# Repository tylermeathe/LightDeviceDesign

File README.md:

# LightDeviceDesign
This read me file is a description of the project.

In this project, one needs to create a light device that functions under different conditions. The light must be able to turn off, turn on at a bright level, be on at an intermediate bright level, be on at a least bright level, and also be on in 2 Hz intervals. The device should be protected by its casing and able to withstand a 3 ft fall as well.

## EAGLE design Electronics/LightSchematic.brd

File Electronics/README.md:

# LightDeviceDesign
This read me file is a description of the project.

In this project, one needs to create a light device that functions under different conditions. The light must be able to turn off, turn on at a bright level, be on at an intermediate bright level, be on at a least bright level, and also be on in 2 Hz intervals. The device should be protected by its casing and able to withstand a 3 ft fall as well.

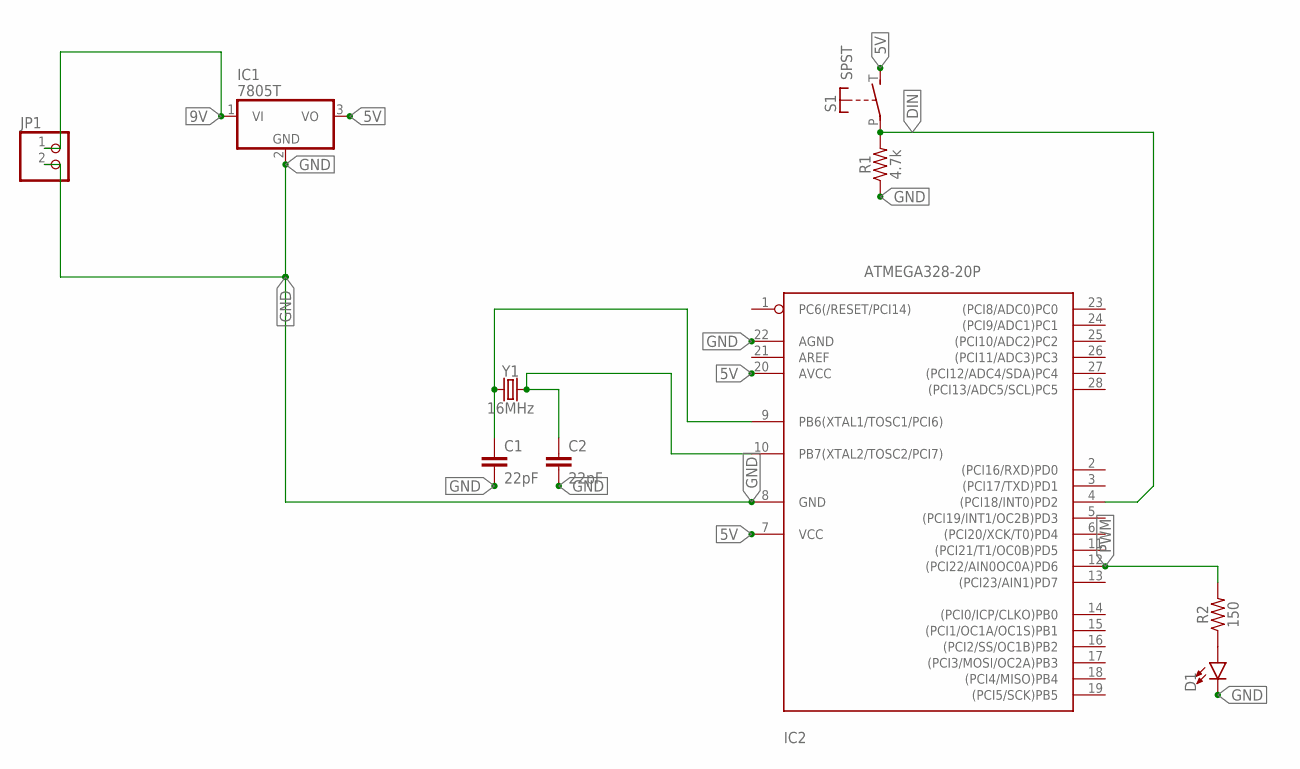
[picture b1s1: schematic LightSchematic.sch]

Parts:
C1, C2: 22pF; 0603
D1: LED1206; LED-1206
IC1: 7805T; TO220H
IC2: ATMEGA328-20P; DIL28-3
JP1: PINHD-1X2; 1X02
R1: 4.7k; 0402
R2: 150; 0402
S1: SPST; JUDCOSPST
Y1: 16MHz; HC49US

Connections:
5V: IC1.3 (VO), IC2.7 (VCC), IC2.20 (AVCC), S1.T (S)
9V: IC1.1 (VI), JP1.1
DIN: IC2.4 ((PCI18/INT0)PD2), R1.2, S1.P
GND: C1.2, C2.2, D1.C, IC1.2 (GND), IC2.8 (GND), IC2.22 (AGND), JP1.2, R1.1
unnamed: C1.1, IC2.9 (PB6(XTAL1/TOSC1/PCI6)), Y1.1
unnamed: C2.1, IC2.10 (PB7(XTAL2/TOSC2/PCI7)), Y1.2
unnamed: D1.A, R2.1
PWM: IC2.12 ((PCI22/AIN0OC0A)PD6), R2.2

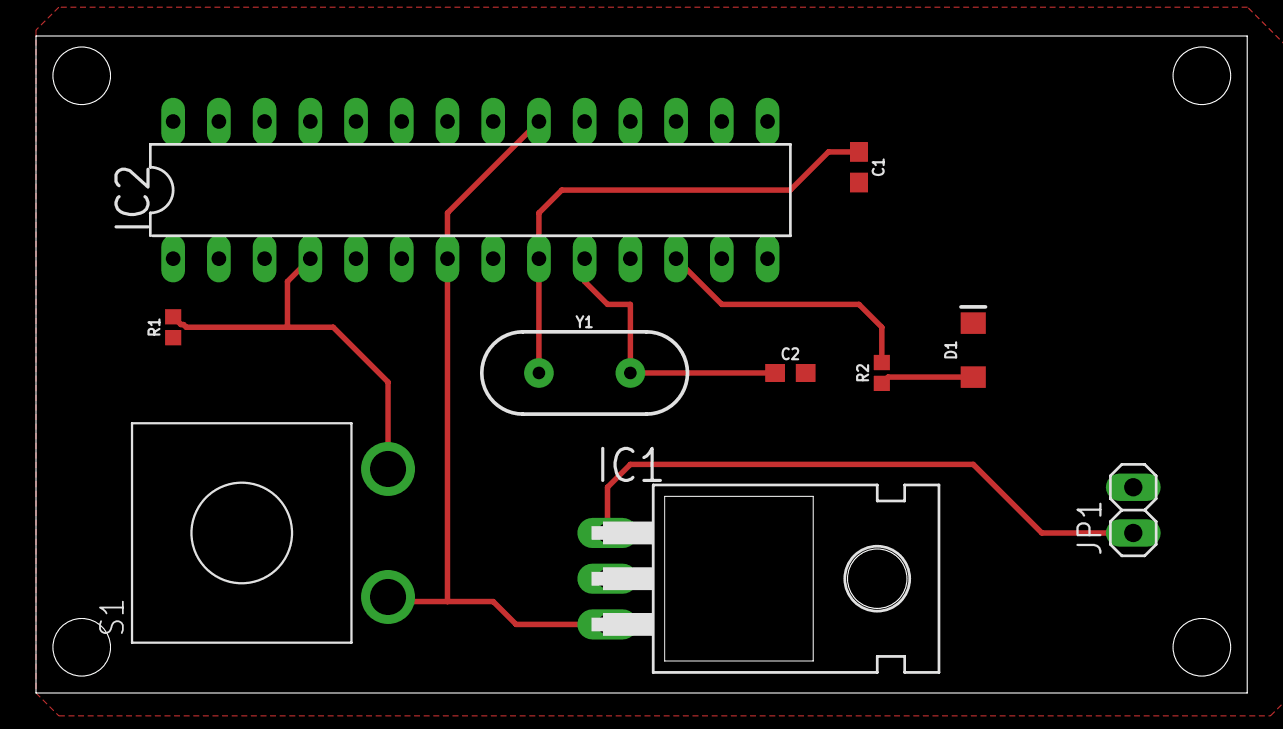
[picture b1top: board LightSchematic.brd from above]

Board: 2 copper layers, 67.3 x 36.5 mm, 10 parts (0 on the bottom side), 8 nets.

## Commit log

2018-11-06 Add EDA schematic PDF to Repo
2018-11-06 Add other folders to repo
2018-11-06 Add flowchart to software repo
2018-11-08 Add updated schematic with ATMEGA328p
2018-11-08 Add Eagle Project to repo for milestone 4 review
2018-11-08 Add v0.2.0 board and schematic for milestone 4
2018-11-08 Add readme to repo
2018-11-08 Add v0.2.1 for milestone 4 review
2018-11-08 add Arduino software v0.2.0
2018-11-19 Added holes to PCB
2018-11-20 Add solidworks casing design
2018-11-20 Added 16 MHz crystal oscillator and 2 22 pF capacitors
2018-11-20 Add JPG of Board
2018-11-27 Changed code after testing
2018-12-09 New Casing for Protoboard
2018-12-09 Add component list
2018-12-14 Add drawings to repo

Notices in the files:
parts and their libraries:
SparkFun-LED: Licensing: Creative Commons ShareAlike 4.0 International - https://creativecommons.org/licenses/by-sa/4.0
